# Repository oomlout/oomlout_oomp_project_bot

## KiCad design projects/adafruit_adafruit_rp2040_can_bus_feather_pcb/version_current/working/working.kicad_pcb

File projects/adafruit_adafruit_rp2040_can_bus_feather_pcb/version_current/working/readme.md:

# OOMP Project  
## Adafruit-RP2040-CAN-Bus-Feather-PCB  by adafruit  
  
oomp key: oomp_projects_flat_adafruit_adafruit_rp2040_can_bus_feather_pcb  
(snippet of original readme)  
  
-- Adafruit RP2040 CAN Bus Feather with MCP2515 CAN Controller - STEMMA QT PCB  
  
<a href="http://www.adafruit.com/products/5724"><br/>  
Click here to purchase one from the Adafruit shop</a>  
  
PCB files for the Adafruit RP2040 CAN Bus Feather with MCP2515 CAN Controller - STEMMA QT.   
  
Format is EagleCAD schematic and board layout  
* https://www.adafruit.com/product/5724  
  
--- Description  
  
If you'd like to quickly get started with CAN bus interfacing, with no soldering required, our Adafruit RP2040 CAN Bus Feather comes ready-to-rock with a microcontroller, CAN chipset and terminal blocks for instant gratification. The controller used is the MCP26525 (aka a MCP2515 with built-in transciever), an extremely popular and well-supported chipset that has drivers in Arduino and CircuitPython and only requires an SPI port and two pins for chip-select and IRQ. Use it to send and receive messages in either standard or extended format at up to 1 Mbps.  
  
Feather is the development board specification from Adafruit, and like its namesake, it is thin, light, and lets you fly! We designed Feather to be a new standard for portable microcontroller cores. We have other boards in the Feather family, check'em out here.  
  
CAN Bus is a small-scale networking standard, originally designed for cars and, yes, busses, but is now used for many robotics or sensor networks that need better range and addressing than I2C and don't have the pins or computational abil  
  full source readme at [readme_src.md](readme_src.md)  
  
source repo at: [https://github.com/adafruit/Adafruit-RP2040-CAN-Bus-Feather-PCB](https://github.com/adafruit/Adafruit-RP2040-CAN-Bus-Feather-PCB)  
## Board  

## Schematic  

[schematic pdf](working_schematic.pdf)  
## Images

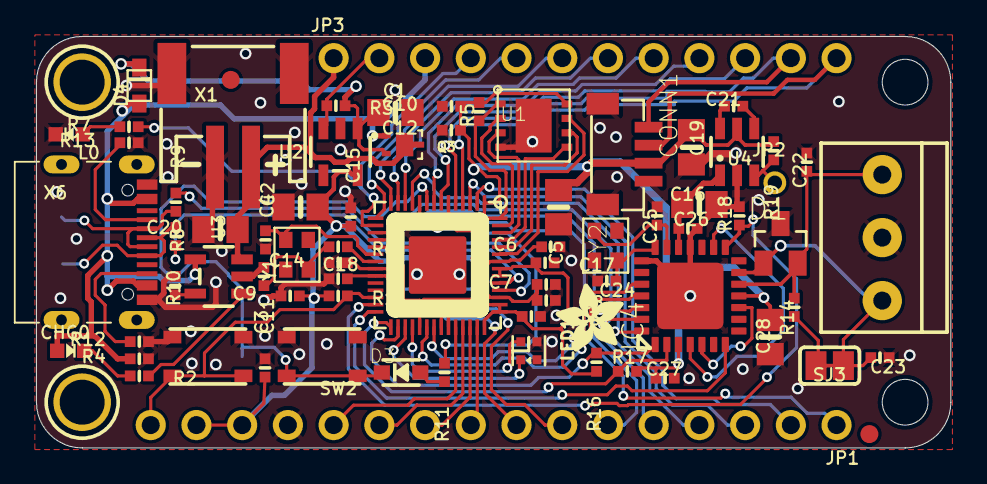
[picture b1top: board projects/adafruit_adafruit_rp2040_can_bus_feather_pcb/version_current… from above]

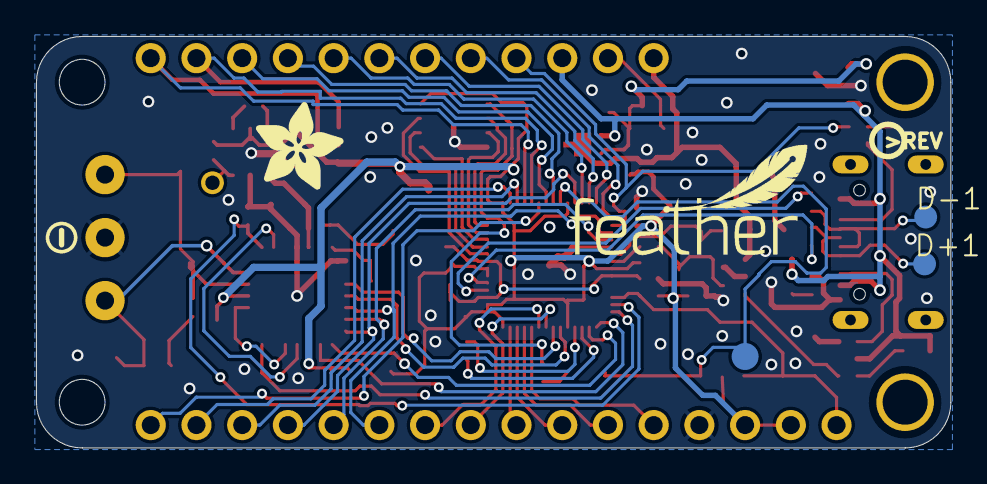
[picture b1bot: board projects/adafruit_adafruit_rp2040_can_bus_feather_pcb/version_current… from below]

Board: 2 copper layers, 50.8 x 22.9 mm, 155 parts (40 on the bottom side), 69 nets.

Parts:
@HOLE0, @HOLE1: (no value)
C1, C4, C5, C16, C19, C20, C28: 10uF/16V; 0805-NO
C2, C3, C24, C25: 22pF; _0402NO
C6, C7, C9, C12, C13, C14, C18, C26, C27: 0.1uF; _0402NO
C8, C10, C11, C15, C17, C21: 1uF/25V; _0402NO
C22, C23: 47pF; _0402NO
CHG0: ORANGE; CHIPLED_0603_NOOUTLINE
CONN1: STEMMA_I2C_QTRA; JST_SH4_RA
D1: PESD1CAN; SOT23
D3: 1N5819; SOD-323_MINI
D4: PMEG2020AEA; SOD-323F
D+1: TPB1,27; B1,27
D-1: TPB1,27; B1,27
IC1: RP2040_QFN56; QFN56_7MM_REDUCEDEPAD
IC4: MCP25625; QFN28-ML_6X6MM
JP1: 1X16_ROUND
JP2: 1X01_2MM
JP3: 1X12_ROUND
L0: RED; CHIPLED_0603_NOOUTLINE
LED1: WS2812B_SK6805_1515; SK6805_1515
NEOPIX1: 3.5mm; TERMBLOCK_1X3-3.5MM
PLABEL0: PLABEL0
PLABEL1: PLABEL1
PLABEL2: PLABEL2
PLABEL3: PLABEL3
PLABEL4: PLABEL4
PLABEL5: PLABEL5
PLABEL6: PLABEL6
PLABEL7: PLABEL7
PLABEL8: PLABEL8
PLABEL9: PLABEL9
PLABEL10: PLABEL10
PLABEL11: PLABEL11
PLABEL12: PLABEL12
PLABEL13: PLABEL13
PLABEL14: PLABEL14
PLABEL15: PLABEL15
PLABEL16: PLABEL16
PLABEL17: PLABEL17
PLABEL18: PLABEL18
PLABEL19: PLABEL19
PLABEL20: PLABEL20
PLABEL21: PLABEL21
PLABEL22: PLABEL22
PLABEL23: PLABEL23
PLABEL24: PLABEL24
PLABEL25: PLABEL25
PLABEL26: PLABEL26
PLABEL27: PLABEL27
PLABEL28: PLABEL28
PLABEL29: PLABEL29
PLABEL30: PLABEL30
PLABEL31: PLABEL31
PLABEL32: PLABEL32
PLABEL33: PLABEL33
PLABEL34: PLABEL34
PLABEL35: PLABEL35
PLABEL36: PLABEL36
PLABEL37: PLABEL37
PLABEL38: PLABEL38
PLABEL39: PLABEL39
PLABEL40: PLABEL40
PLABEL41: PLABEL41
PLABEL42: PLABEL42
PLABEL43: PLABEL43
PLABEL44: PLABEL44
PLABEL45: PLABEL45
PLABEL46: PLABEL46
PLABEL47: PLABEL47
PLABEL48: PLABEL48
PLABEL49: PLABEL49
PLABEL50: PLABEL50
PLABEL51: PLABEL51
PLABEL52: PLABEL52
PLABEL53: PLABEL53
PLABEL54: PLABEL54
PLABEL55: PLABEL55
PLABEL56: PLABEL56
PLABEL57: PLABEL57
PLABEL58: PLABEL58
PLABEL59: PLABEL59
PLABEL60: PLABEL60
PLABEL61: PLABEL61
PLABEL62: PLABEL62
PLABEL63: PLABEL63
PLABEL64: PLABEL64
PLABEL65: PLABEL65
PLABEL66: PLABEL66
PLABEL67: PLABEL67
PLABEL68: PLABEL68
PLABEL69: PLABEL69
Q3: DMG3415UFY; DFN2015-3
R1, R2, R3, R4, R5, R7, R16, R17, R18, R19: 10K; _0402NO
R6, R11: 1K; _0402NO
R8, R12, R13: 5.1K; _0402NO
R9, R10: 22 ohm; _0402NO
R14: 120; _0402NO
SJ3: SOLDERJUMPER_CLOSEDWIRE
SW1, SW2: RKB2; BTN_RKB2_4.6X2.8
TP3: TESTPOINT_ROUND_1.5MM_NO
U1: 8MB QSPI; USON8_4X4
U2: RT9080-3.3; SOT23-5
U3: MCP73831T-2ACI/OT; SOT23-5
U4: AP3602; SOT23-6
U$13: PCBFEAT-REV-040
U$31, U$32: MOUNTINGHOLE2.5; MOUNTINGHOLE_2.5_PLATED
U$34, U$35: FIDUCIAL_1MM
U$42: ADAFRUIT_3.5MM
U$53: SYMBOL_MINUS
U$54: ADAFRUIT_5MM
U$60: FEATHERLOGO_SMALL
X1: JSTPH; JSTPH2_BATT
X6: USB Type C; USB_C_CUSB31-CFM2AX-01-X
Y1: 12MHz/12pF; CRYSTAL_2.5X2
Y2: 16MHz 12pF; CRYSTAL_2.5X2

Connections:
1.2V: C6.2, C7.2, C8.1, C18.2, IC1.23, IC1.45, IC1.50
5.0V: C16.1, C26.2, IC4.19, U4.1
5V_SHDN: JP2.1, R19.2, U4.3
+3V3: C4.1, C5.1, C9.1, C10.1, C11.1, C12.1, C13.1, C14.1, C15.1, C17.1, C19.1, C27.2, C28.1, CONN1.2, IC1.1, IC1.10, IC1.22, IC1.33, IC1.42, IC1.43, IC1.44, IC1.48, IC1.49, IC4.3, IC4.11, JP1.14, JP1.15, R1.1, R5.2, R16.2, R17.2, R19.1, U1.8, U2.5, U4.5
A0: IC1.38, JP1.12
A1: IC1.39, JP1.11
A2: IC1.40, JP1.10
A3: IC1.41, JP1.9
CAN_CS: IC1.30, IC4.1, R16.1
CAN_H: C23.1, D1.1, IC4.13, NEOPIX1.3, SJ3.2
CAN_INT: IC1.34, IC4.25
CAN_L: C22.2, D1.2, IC4.12, NEOPIX1.1, R14.1
CAN_RESET: IC1.29, IC4.2, R17.1
CAN_STBY: IC1.27, IC4.15, R18.1
CC1: R13.2, X6.A5
CC2: R12.2, X6.B5
D4: IC1.6, JP1.1
D5: IC1.7, JP3.10
D6: IC1.8, JP3.9
D9: IC1.12, JP3.8
D10: IC1.13, JP3.7
D11: IC1.14, JP3.6
D12: IC1.15, JP3.5
D13: IC1.16, JP3.4, R7.1
D24: IC1.36, JP1.8
D25: IC1.37, JP1.7
D+: IC1.47, R10.2
D-: IC1.46, R9.2
EN: JP3.2, R3.1, U2.3
GND: C1.2, C2.1, C3.1, C4.2, C5.2, C6.1, C7.1, C8.2, C9.2, C10.2, C11.2, C12.2, C13.2, C14.2, C15.2, C16.2, C17.2, C18.1, C19.2, C20.2, C22.1, C23.2, C24.1, C25.1, C26.1, C27.1, C28.2, CONN1.1, CONN1.MT1, CONN1.MT2, D1.3, IC1.19, IC1.P$1, IC4.18, IC4.22, IC4.EXP, JP1.13, L0.C, LED1.4, NEOPIX1.2, R4.1, R8.2, R12.1, R13.1, R18.2, SW1.B, SW1.B', SW2.B, SW2.B', U1.4, U1.PAD, U2.2, U3.2, U4.2, X1.1, X1.NC1, X1.NC2, X6.A1B12, X6.B1A12
MISO: IC1.11, IC4.28, JP1.4
MOSI: IC1.18, IC4.27, JP1.5
unnamed: CHG0.C, R2.1
unnamed: L0.A, R7.2
unnamed: R2.2, U3.1
unnamed: R8.1, U3.5
unnamed: C2.2, IC1.20, Y1.3
unnamed: C3.2, R6.1, Y1.1
unnamed: IC1.21, R6.2
unnamed: C21.1, U4.4
unnamed: C21.2, U4.6
unnamed: R14.2, SJ3.1
unnamed: IC4.5, IC4.10
unnamed: IC4.4, IC4.16
unnamed: D3.A, R11.2
NEOPIXEL: IC1.32, LED1.1
NEOPIX_PWR: IC1.31, LED1.2
OSC1: C24.2, IC4.21, Y2.3
OSC2: C25.2, IC4.20, Y2.1
QSPI_CS: IC1.56, R5.1, R11.1, U1.1
QSPI_DATA[0]: IC1.53, U1.5
QSPI_DATA[1]: IC1.55, U1.2
QSPI_DATA[2]: IC1.54, U1.3
QSPI_DATA[3]: IC1.51, U1.7
QSPI_SCK: IC1.52, U1.6
RX: IC1.3, JP1.3
RX0BF: IC1.35, IC4.24
SCK: IC1.17, IC4.26, JP1.6
SCL: CONN1.4, IC1.5, JP3.11
SDA: CONN1.3, IC1.4, JP3.12
TX: IC1.2, JP1.2
TX0RTS: IC1.28, IC4.7
USBBOOT: D3.C, IC1.9, SW2.A, SW2.A', TP3.P$1
USB_D+: D+1.TP, R10.1, X6.A6, X6.B6
USB_D-: D-1.TP, R9.1, X6.A7, X6.B7
VBAT: C20.1, JP3.1, Q3.3, U3.3, X1.2
VBUS: CHG0.A, D4.A, JP3.3, Q3.1, R4.2, U3.4, X6.A4B9, X6.B4A9
VHI: C1.1, D4.C, Q3.2, R3.2, U2.1
~RESET: IC1.26, JP1.16, R1.2, SW1.A, SW1.A'

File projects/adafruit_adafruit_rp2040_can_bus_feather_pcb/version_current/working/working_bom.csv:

"Id";"Designator";"Footprint";"Quantity";"Designation";"Supplier and ref";
1;"C14,C13,C26,C27,C18,C6,C7,C9,C12";"_0402NO";9;"0.1uF";;;
2;"C15,C8,C17,C10,C21,C11";"_0402NO";6;"1uF/25V";;;
3;"PLABEL5";"PLABEL5";1;"";;;
4;"L0";"CHIPLED_0603_NOOUTLINE";1;"RED";;;
5;"@HOLE0,@HOLE1";"";2;"";;;
6;"PLABEL3";"PLABEL3";1;"";;;
7;"C1,C20,C5,C28,C16,C4,C19";"0805-NO";7;"10uF/16V";;;
8;"R18,R2,R17,R4,R5,R3,R1,R7,R16,R19";"_0402NO";10;"10K";;;
9;"PLABEL33";"PLABEL33";1;"";;;
10;"CHG0";"CHIPLED_0603_NOOUTLINE";1;"ORANGE";;;
11;"PLABEL26";"PLABEL26";1;"";;;
12;"PLABEL21";"PLABEL21";1;"";;;
13;"SW1,SW2";"BTN_RKB2_4.6X2.8";2;"RKB2";;;
14;"Q3";"DFN2015-3";1;"DMG3415UFY";;;
15;"PLABEL19";"PLABEL19";1;"";;;
16;"U$42";"ADAFRUIT_3.5MM";1;"";;;
17;"PLABEL23";"PLABEL23";1;"";;;
18;"U1";"USON8_4X4";1;"8MB QSPI";;;
19;"PLABEL4";"PLABEL4";1;"";;;
20;"PLABEL8";"PLABEL8";1;"";;;
21;"PLABEL0";"PLABEL0";1;"";;;
22;"SJ3";"SOLDERJUMPER_CLOSEDWIRE";1;"";;;
23;"JP3";"1X12_ROUND";1;"";;;
24;"PLABEL34";"PLABEL34";1;"";;;
25;"IC1";"QFN56_7MM_REDUCEDEPAD";1;"RP2040_QFN56";;;
26;"D4";"SOD-323F";1;"PMEG2020AEA";;;
27;"PLABEL15";"PLABEL15";1;"";;;
28;"JP1";"1X16_ROUND";1;"";;;
29;"R11,R6";"_0402NO";2;"1K";;;
30;"D1";"SOT23";1;"PESD1CAN";;;
31;"PLABEL24";"PLABEL24";1;"";;;
32;"U4";"SOT23-6";1;"AP3602";;;
33;"PLABEL27";"PLABEL27";1;"";;;
34;"R13,R12,R8";"_0402NO";3;"5.1K";;;
35;"C3,C25,C24,C2";"_0402NO";4;"22pF";;;
36;"PLABEL1";"PLABEL1";1;"";;;
37;"Y2";"CRYSTAL_2.5X2";1;"16MHz 12pF";;;
38;"Y1";"CRYSTAL_2.5X2";1;"12MHz/12pF";;;
39;"PLABEL25";"PLABEL25";1;"";;;
40;"PLABEL2";"PLABEL2";1;"";;;
41;"CONN1";"JST_SH4_RA";1;"STEMMA_I2C_QTRA";;;
42;"PLABEL30";"PLABEL30";1;"";;;
43;"X6";"USB_C_CUSB31-CFM2AX-01-X";1;"USB Type C";;;
44;"PLABEL12";"PLABEL12";1;"";;;
45;"U$32,U$31";"MOUNTINGHOLE_2.5_PLATED";2;"MOUNTINGHOLE2.5";;;
46;"PLABEL35";"PLABEL35";1;"";;;
47;"PLABEL6";"PLABEL6";1;"";;;
48;"PLABEL31";"PLABEL31";1;"";;;
49;"R14";"_0402NO";1;"120";;;
50;"PLABEL14";"PLABEL14";1;"";;;
51;"R9,R10";"_0402NO";2;"22 ohm";;;
52;"X1";"JSTPH2_BATT";1;"JSTPH";;;
53;"PLABEL17";"PLABEL17";1;"";;;
54;"U3";"SOT23-5";1;"MCP73831T-2ACI/OT";;;
55;"D3";"SOD-323_MINI";1;"1N5819";;;
56;"PLABEL9";"PLABEL9";1;"";;;
57;"PLABEL11";"PLABEL11";1;"";;;
58;"PLABEL16";"PLABEL16";1;"";;;
59;"LED1";"SK6805_1515";1;"WS2812B_SK6805_1515";;;
60;"U2";"SOT23-5";1;"RT9080-3.3";;;
61;"PLABEL7";"PLABEL7";1;"";;;
62;"U$34,U$35";"FIDUCIAL_1MM";2;"FIDUCIAL_1MM";;;
63;"PLABEL10";"PLABEL10";1;"";;;
64;"PLABEL28";"PLABEL28";1;"";;;
65;"PLABEL32";"PLABEL32";1;"";;;
66;"JP2";"1X01_2MM";1;"";;;
67;"C23,C22";"_0402NO";2;"47pF";;;
68;"PLABEL18";"PLABEL18";1;"";;;
69;"PLABEL29";"PLABEL29";1;"";;;
70;"PLABEL20";"PLABEL20";1;"";;;
71;"PLABEL22";"PLABEL22";1;"";;;
72;"PLABEL36";"PLABEL36";1;"";;;
73;"NEOPIX1";"TERMBLOCK_1X3-3.5MM";1;"3.5mm";;;
74;"PLABEL13";"PLABEL13";1;"";;;
75;"IC4";"QFN28-ML_6X6MM";1;"MCP25625";;;
76;"PLABEL42";"PLABEL42";1;"";;;
77;"PLABEL44";"PLABEL44";1;"";;;
78;"PLABEL64";"PLABEL64";1;"";;;
79;"U$13";"PCBFEAT-REV-040";1;"";;;
80;"PLABEL40";"PLABEL40";1;"";;;
81;"U$53";"SYMBOL_MINUS";1;"";;;
82;"PLABEL62";"PLABEL62";1;"";;;
83;"PLABEL47";"PLABEL47";1;"";;;
84;"PLABEL48";"PLABEL48";1;"";;;
85;"PLABEL58";"PLABEL58";1;"";;;
86;"PLABEL59";"PLABEL59";1;"";;;
87;"TP3";"TESTPOINT_ROUND_1.5MM_NO";1;"";;;
88;"PLABEL56";"PLABEL56";1;"";;;
89;"PLABEL63";"PLABEL63";1;"";;;
90;"PLABEL53";"PLABEL53";1;"";;;
91;"PLABEL69";"PLABEL69";1;"";;;
92;"PLABEL51";"PLABEL51";1;"";;;
93;"PLABEL50";"PLABEL50";1;"";;;
94;"PLABEL37";"PLABEL37";1;"";;;
95;"PLABEL67";"PLABEL67";1;"";;;
96;"U$60";"FEATHERLOGO_SMALL";1;"";;;
97;"PLABEL65";"PLABEL65";1;"";;;
98;"PLABEL54";"PLABEL54";1;"";;;
99;"PLABEL38";"PLABEL38";1;"";;;
100;"PLABEL55";"PLABEL55";1;"";;;
101;"PLABEL57";"PLABEL57";1;"";;;
102;"PLABEL66";"PLABEL66";1;"";;;
103;"PLABEL49";"PLABEL49";1;"";;;
104;"PLABEL68";"PLABEL68";1;"";;;
105;"D+1,D-1";"B1,27";2;"TPB1,27";;;
106;"U$54";"ADAFRUIT_5MM";1;"";;;
107;"PLABEL61";"PLABEL61";1;"";;;
108;"PLABEL43";"PLABEL43";1;"";;;
109;"PLABEL52";"PLABEL52";1;"";;;
110;"PLABEL60";"PLABEL60";1;"";;;
111;"PLABEL46";"PLABEL46";1;"";;;
112;"PLABEL45";"PLABEL45";1;"";;;
113;"PLABEL39";"PLABEL39";1;"";;;
114;"PLABEL41";"PLABEL41";1;"";;;

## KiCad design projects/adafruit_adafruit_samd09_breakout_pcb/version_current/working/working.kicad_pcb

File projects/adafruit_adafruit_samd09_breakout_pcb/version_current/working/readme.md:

# OOMP Project  
## Adafruit-SAMD09-Breakout-PCB  by adafruit  
  
oomp key: oomp_projects_flat_adafruit_adafruit_samd09_breakout_pcb  
(snippet of original readme)  
  
-- Adafruit SAMD09 Breakout PCB  
  
<a href="http://www.adafruit.com/products/3657"><br/>  
Click here to purchase one from the Adafruit shop</a>  
  
PCB files for the Adafruit SAMD09 microcontroller breakout  
  
Format is EagleCAD schematic and board layout  
  
For more details, check out the product page at  
* https://www.adafruit.com/products/3657  
  
--- Description  
  
Adafruit seesaw is a near-universal converter framework which allows you to add add and extend hardware support to any I2C-capable microcontroller or microcomputer. Instead of getting separate I2C GPIO expanders, ADCs, PWM drivers, etc, seesaw can be configured to give a wide range of capabilities.  
  
For example, our ATSAMD09 breakout with seesaw gives you  
  
* 3 x 12-bit ADC inputs  
* 3 x 8-bit PWM outputs  
* 7 x GPIO with selectable pullup or pulldown  
* 1 x NeoPixel output (up to 340 pixels)  
* 1 x EEPROM with 64 byte of NVM memory (handy for storing small access tokens or MAC addresses)  
* 1 x Interrupt output that can be triggered by any of the accessories  
* 2 x I2C address selection pins  
* 1 x Activity LED  
  
But you can reprogram and reconfigure the chip to have more or less of each peripheral - as long as it fits into the ATSAMD09D14's firmware! For example, there's also a UART converter but it isn't included in the default firmware.  
  
The ATSAMD09 breakout is great for development of seesaw capabilities (we use it in-house for our design work) or you can use it as-is to give you  
  full source readme at [readme_src.md](readme_src.md)  
  
source repo at: [https://github.com/adafruit/Adafruit-SAMD09-Breakout-PCB](https://github.com/adafruit/Adafruit-SAMD09-Breakout-PCB)  
## Board  

## Schematic  

[schematic pdf](working_schematic.pdf)  
## Images

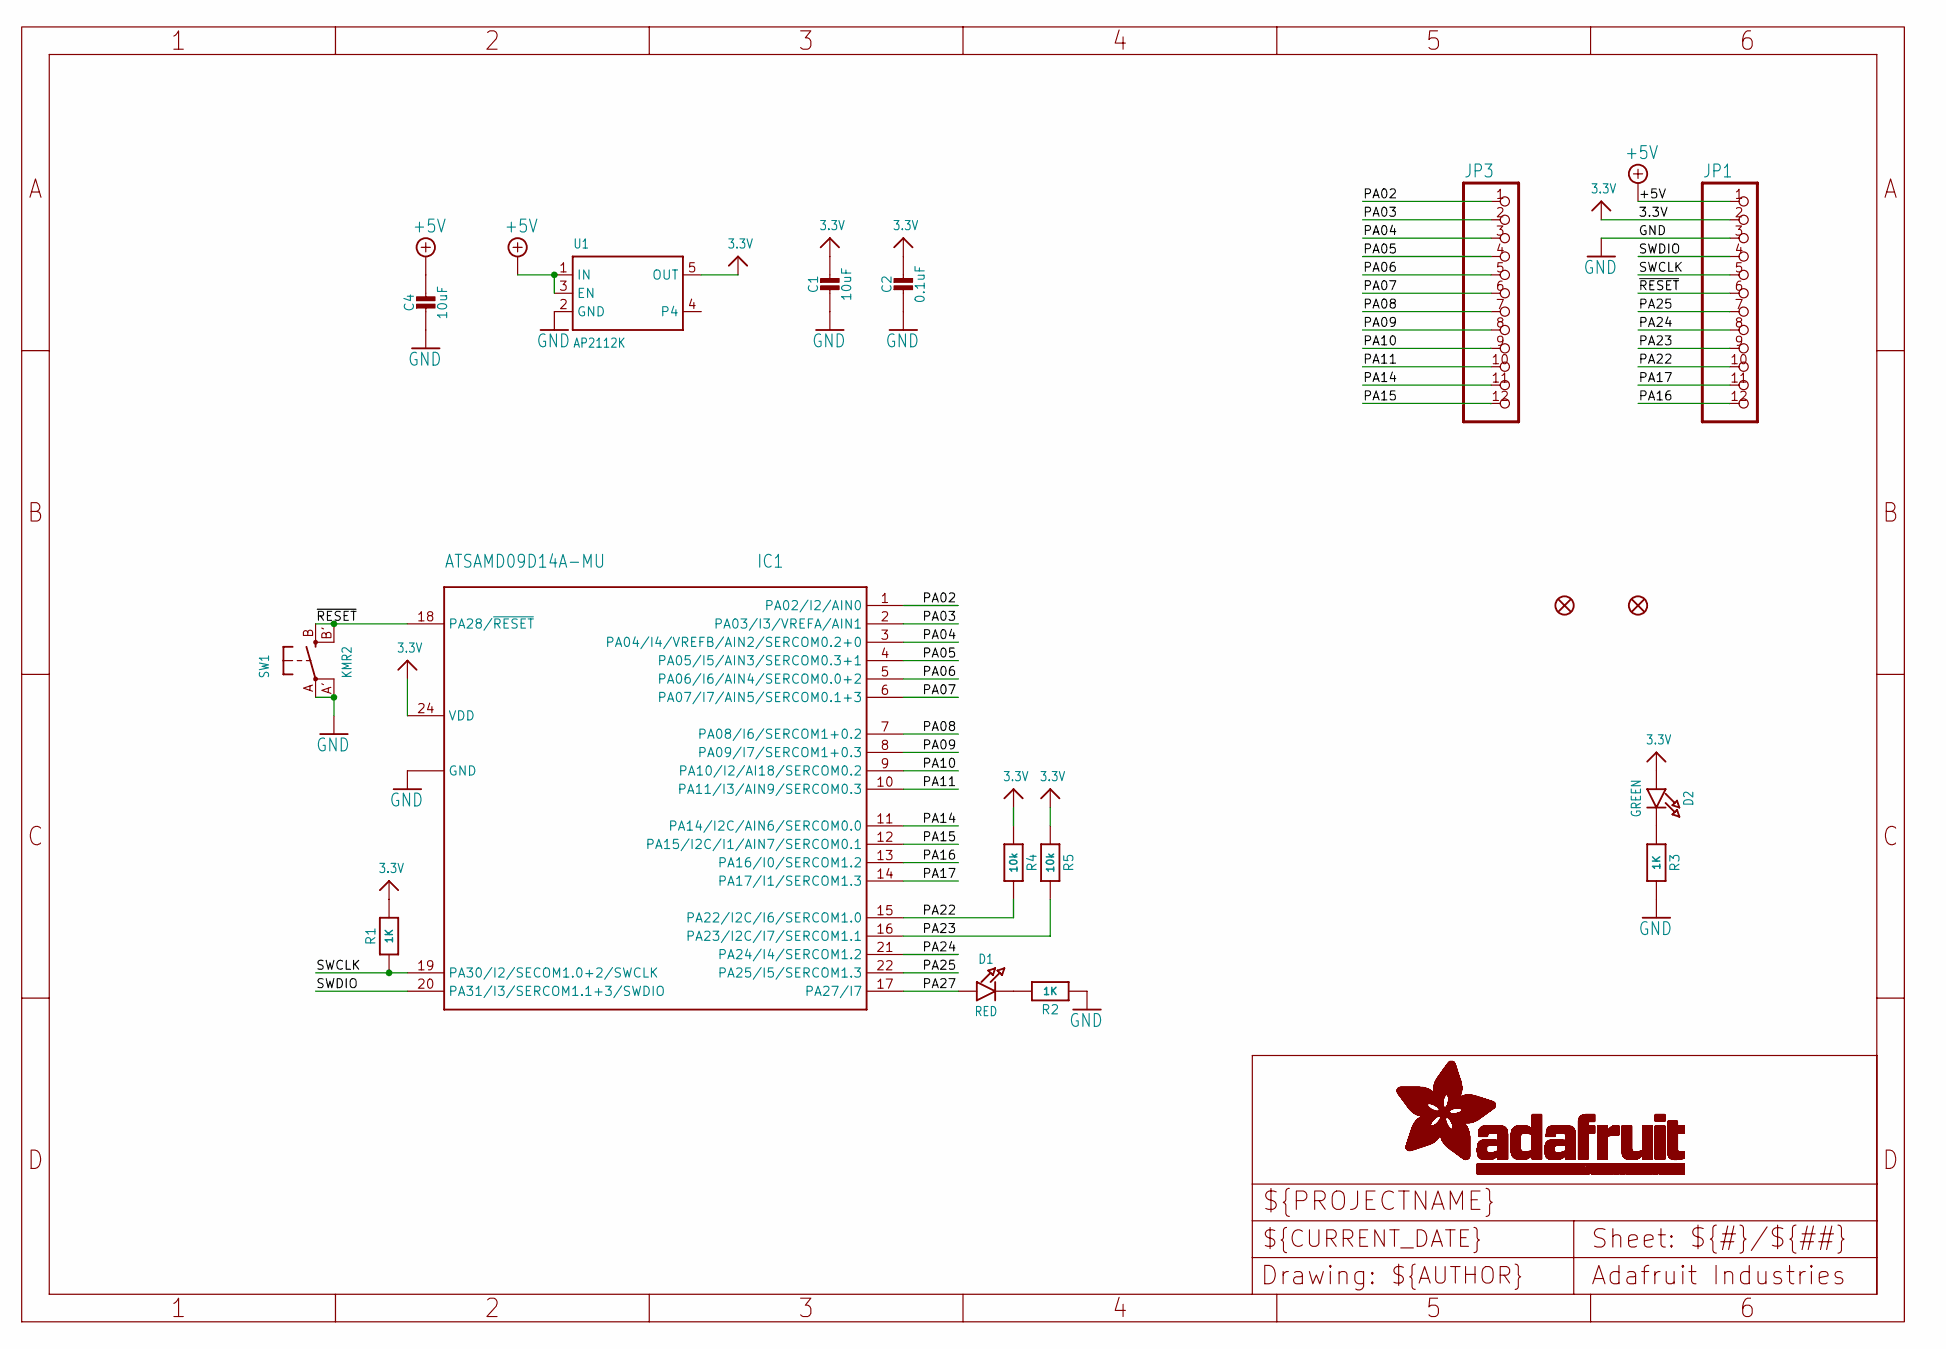
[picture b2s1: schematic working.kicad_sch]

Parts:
C1, C4: 10uF; 0805-NO
C2: 0.1uF; 0603-NO
D1: RED; CHIPLED_0805_NOOUTLINE
D2: GREEN; CHIPLED_0805_NOOUTLINE
FID1, FID2: FIDUCIAL""; FIDUCIAL_1MM
IC1: ATSAMD09D14A-MU; QFN24_4MM
JP1, JP3: HEADER-1X1276MIL; 1X12_ROUND_76MIL
R1, R2, R3: 1K; 0603-NO
R4, R5: 10k; 0603-NO
SW1: KMR2; BTN_KMR2_4.6X2.8
U1: AP2112K; SOT23-5

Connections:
3.3V: C1.1, C2.1, D2.A, IC1.24 (VDD), JP1.2, R1.2, R4.1, R5.1, U1.5 (OUT)
+5V: C4.1, JP1.1, U1.1 (IN), U1.3 (EN)
GND: C1.2, C2.2, C4.2, IC1.23 (GND), IC1.THERM (GND), JP1.3, R2.1, R3.2, SW1.A, SW1.A' (P1), U1.2 (GND)
unnamed: D1.C, R2.2
unnamed: D2.C, R3.1
PA02: IC1.1 (PA02/I2/AIN0), JP3.1
PA03: IC1.2 (PA03/I3/VREFA/AIN1), JP3.2
PA04: IC1.3 (PA04/I4/VREFB/AIN2/SERCOM0.2+0), JP3.3
PA05: IC1.4 (PA05/I5/AIN3/SERCOM0.3+1), JP3.4
PA06: IC1.5 (PA06/I6/AIN4/SERCOM0.0+2), JP3.5
PA07: IC1.6 (PA07/I7/AIN5/SERCOM0.1+3), JP3.6
PA08: IC1.7 (PA08/I6/SERCOM1+0.2), JP3.7
PA09: IC1.8 (PA09/I7/SERCOM1+0.3), JP3.8
PA10: IC1.9 (PA10/I2/AI18/SERCOM0.2), JP3.9
PA11: IC1.10 (PA11/I3/AIN9/SERCOM0.3), JP3.10
PA14: IC1.11 (PA14/I2C/AIN6/SERCOM0.0), JP3.11
PA15: IC1.12 (PA15/I2C/I1/AIN7/SERCOM0.1), JP3.12
PA16: IC1.13 (PA16/I0/SERCOM1.2), JP1.12
PA17: IC1.14 (PA17/I1/SERCOM1.3), JP1.11
PA22: IC1.15 (PA22/I2C/I6/SERCOM1.0), JP1.10, R4.2
PA23: IC1.16 (PA23/I2C/I7/SERCOM1.1), JP1.9, R5.2
PA24: IC1.21 (PA24/I4/SERCOM1.2), JP1.8
PA25: IC1.22 (PA25/I5/SERCOM1.3), JP1.7
PA27: D1.A, IC1.17 (PA27/I7)
SWCLK: IC1.19 (PA30/I2/SECOM1.0+2/SWCLK), JP1.5, R1.1
SWDIO: IC1.20 (PA31/I3/SERCOM1.1+3/SWDIO), JP1.4
~RESET: IC1.18 (PA28/~RESET), JP1.6, SW1.B (S), SW1.B' (S1)

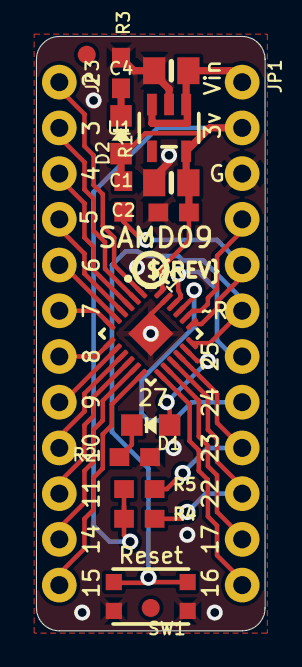
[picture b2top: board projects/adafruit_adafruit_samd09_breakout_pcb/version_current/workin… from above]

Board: 2 copper layers, 12.7 x 33.0 mm, 19 parts (1 on the bottom side), 27 nets.

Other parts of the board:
U$7: SEESAW_LOGO
U$12: PCBFEAT-REV-040

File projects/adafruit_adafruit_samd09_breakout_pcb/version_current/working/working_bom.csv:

Row,Description,Part,References,Value,Footprint,Quantity Per PCB,Status,Datasheet
1,,CAP_CERAMIC0603_NO,C2,0.1uF,0603-NO,1, ,
2,,CAP_CERAMIC0805-NOOUTLINE,C1 C4,10uF,0805-NO,2, ,
3,,LED0805_NOOUTLINE,D2,GREEN,CHIPLED_0805_NOOUTLINE,1, ,
4,,LED0805_NOOUTLINE,D1,RED,CHIPLED_0805_NOOUTLINE,1, ,
5,,ATSAMD09D14A-MU,IC1,ATSAMD09D14A-MU,QFN24_4MM,1, ,
6,,HEADER-1X1276MIL,JP1 JP3,HEADER-1X1276MIL,1X12_ROUND_76MIL,2, ,
7,,RESISTOR_0603_NOOUT,R1 R2 R3,1K,0603-NO,3, ,
8,,RESISTOR_0603_NOOUT,R4 R5,10k,0603-NO,2, ,
9,,SWITCH_TACT_SMT4.6X2.8,SW1,KMR2,BTN_KMR2_4.6X2.8,1, ,
10,,VREG_SOT23-5,U1,AP2112K,SOT23-5,1, ,





Project info:
Schematic:,working
Variant:,default
Revision:,
Date:,2023-08-03_17-21-23
KiCad Version:,7.0.6-7.0.6~ubuntu22.04.1
Statistics:
Component Groups:,10
Component Count:,15 (0 SMD/ 0 THT)
Fitted Components:,15 (0 SMD/ 0 THT)
Number of PCBs:,1
Total Components:,15

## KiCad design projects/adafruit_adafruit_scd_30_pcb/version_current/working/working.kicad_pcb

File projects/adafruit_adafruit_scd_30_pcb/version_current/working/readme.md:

# OOMP Project  
## Adafruit-SCD-30-PCB  by adafruit  
  
oomp key: oomp_projects_flat_adafruit_adafruit_scd_30_pcb  
(snippet of original readme)  
  
-- Adafruit SCD-30 NDIR CO2 Temperature and Humidity Sensor PCB  
  
<a href="http://www.adafruit.com/products/4867"><br/>  
Click here to purchase one from the Adafruit shop</a>  
  
PCB files for the Adafruit SCD-30 NDIR CO2 Temperature and Humidity Sensor.   
  
Format is EagleCAD schematic and board layout  
* https://www.adafruit.com/product/4867  
  
--- Description  
  
INSERT PRODUCT COPY HERE  
  
--- License  
  
Adafruit invests time and resources providing this open source design, please support Adafruit and open-source hardware by purchasing products from [Adafruit](https://www.adafruit.com)!  
  
Designed by Limor Fried/Ladyada for Adafruit Industries.  
  
Creative Commons Attribution/Share-Alike, all text above must be included in any redistribution.   
See license.txt for additional details.  
  
  full source readme at [readme_src.md](readme_src.md)  
  
source repo at: [https://github.com/adafruit/Adafruit-SCD-30-PCB](https://github.com/adafruit/Adafruit-SCD-30-PCB)  
## Board  

## Schematic  

[schematic pdf](working_schematic.pdf)  
## Images

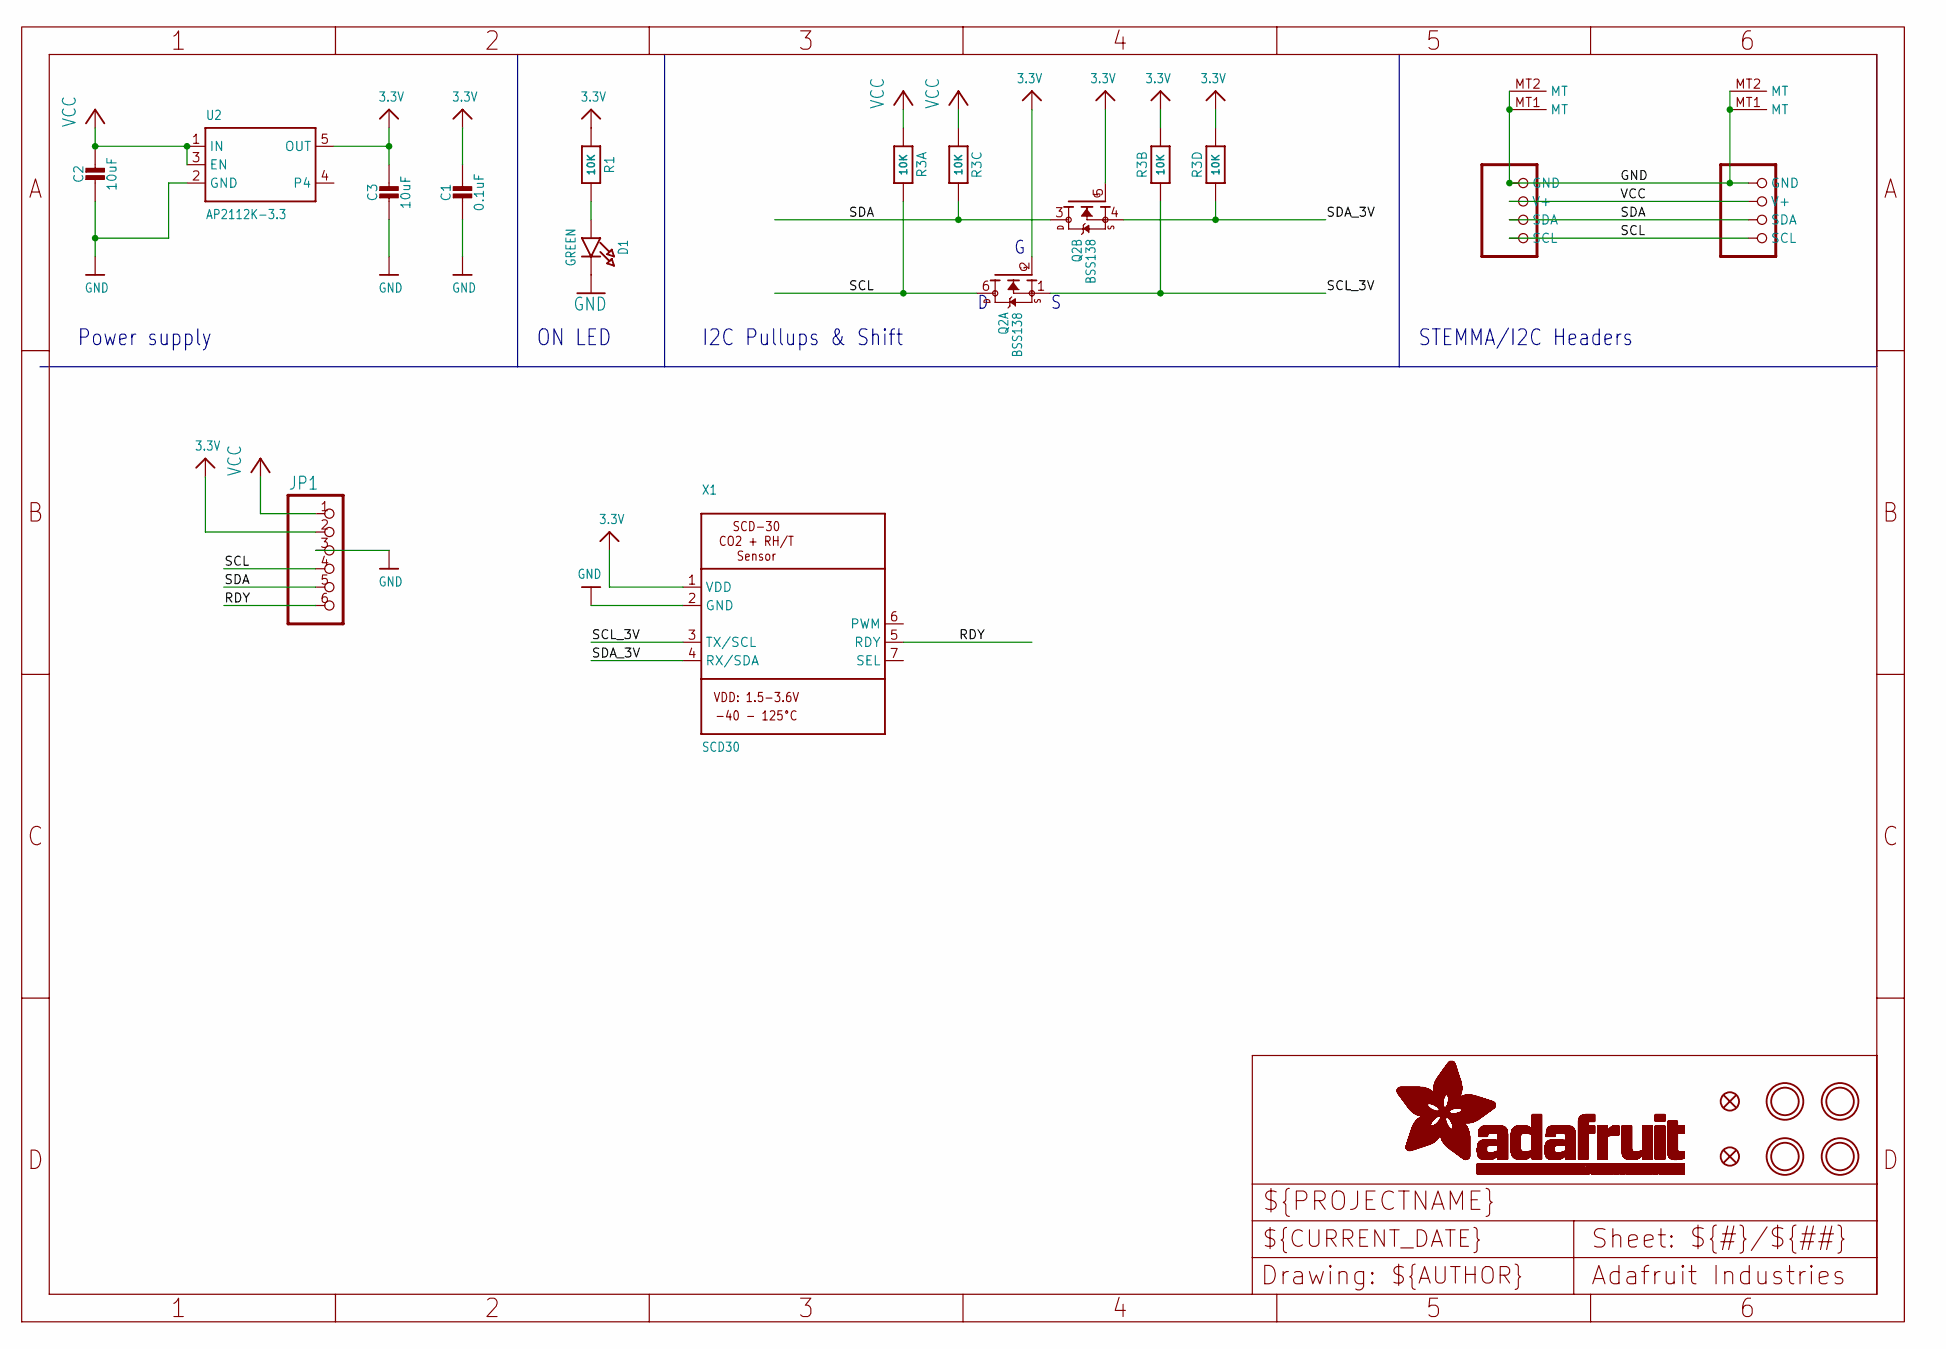
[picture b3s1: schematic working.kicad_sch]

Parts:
C1: 0.1uF; 0603-NO
C2, C3: 10uF; 0805-NO
CONN3, CONN4: STEMMA_I2C_QT; JST_SH4
D1: GREEN; CHIPLED_0603_NOOUTLINE
FID3, FID4: FIDUCIAL_1MM
JP1: HEADER-1X670MIL; 1X06_ROUND_70
Q2: BSS138; SOT363
R1: 10K; 0603-NO
R3: 10K; RESPACK_4X0603
U2: AP2112K-3.3; SOT23-5
U$1, U$17, U$19, U$21: MOUNTINGHOLE2.5; MOUNTINGHOLE_2.5_PLATED
X1: SCD30

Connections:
3.3V: C1.1, C3.1, JP1.2, Q2.2 (G), Q2.5 (G), R1.1, R3.2 (1), R3.4 (1), U2.5 (OUT), X1.1 (VDD)
GND: C1.2, C2.2, C3.2, CONN3.1 (GND), CONN3.MT1 (MT), CONN3.MT2 (MT), CONN4.1 (GND), CONN4.MT1 (MT), CONN4.MT2 (MT), D1.C, JP1.3, U2.2 (GND), X1.2 (GND)
unnamed: D1.A, R1.2
RDY: JP1.6, X1.5 (RDY)
SCL: CONN3.4 (SCL), CONN4.4 (SCL), JP1.4, Q2.6 (D), R3.8 (2)
SCL_3V: Q2.1 (S), R3.7 (2), X1.3 (TX/SCL)
SDA: CONN3.3 (SDA), CONN4.3 (SDA), JP1.5, Q2.3 (D), R3.6 (2)
SDA_3V: Q2.4 (S), R3.5 (2), X1.4 (RX/SDA)
VCC: C2.1, CONN3.2 (V+), CONN4.2 (V+), JP1.1, R3.1, R3.3 (1), U2.1 (IN), U2.3 (EN)

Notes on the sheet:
ON LED
STEMMA/I2C Headers
Power supply
I2C Pullups & Shift

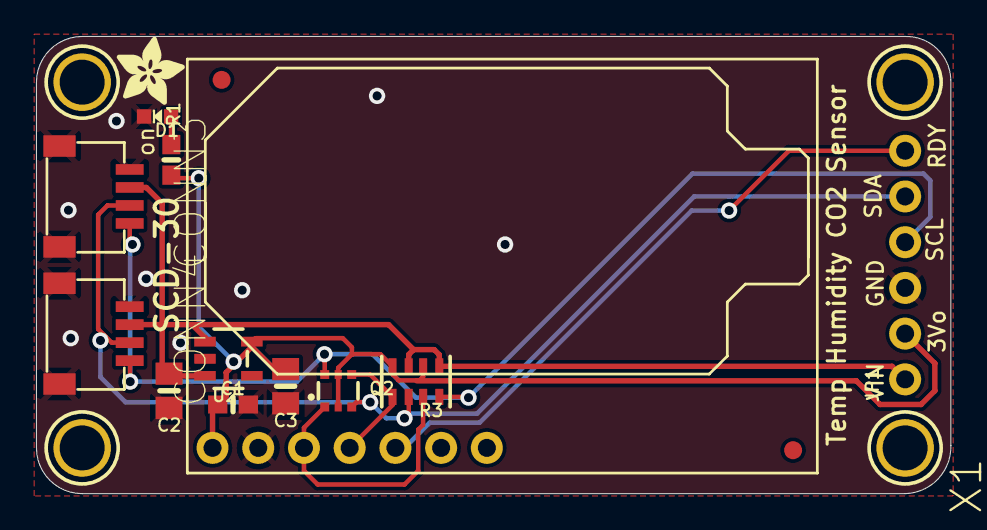
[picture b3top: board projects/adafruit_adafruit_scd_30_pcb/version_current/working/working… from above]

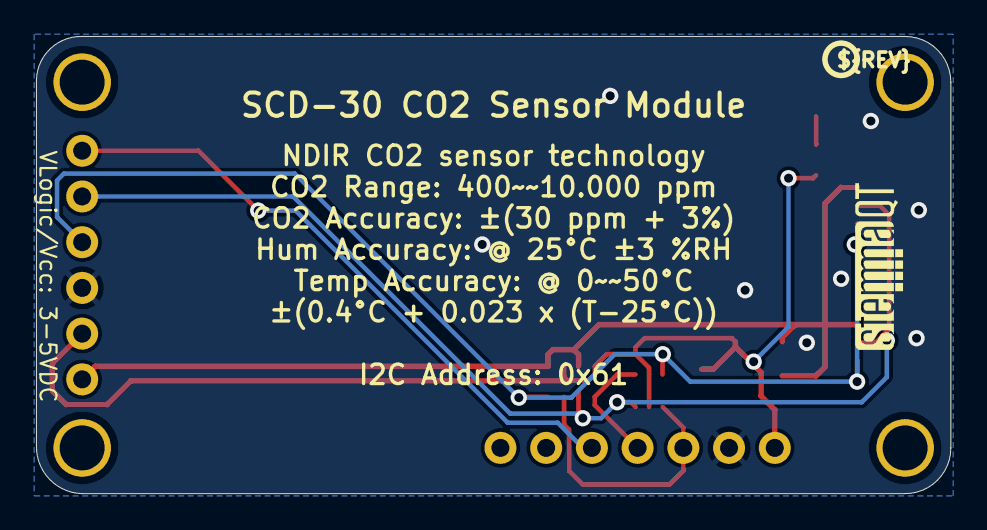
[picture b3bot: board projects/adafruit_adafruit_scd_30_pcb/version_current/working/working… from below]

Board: 2 copper layers, 50.8 x 25.4 mm, 21 parts (2 on the bottom side), 9 nets.

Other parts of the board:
U$22: ADAFRUIT_3.5MM
U$25: PCBFEAT-REV-040
U$30: STEMMAQT

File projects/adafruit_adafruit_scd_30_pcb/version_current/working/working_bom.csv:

Row,Description,Part,References,Value,Footprint,Quantity Per PCB,Status,Datasheet
1,,CAP_CERAMIC0603_NO,C1,0.1uF,0603-NO,1, ,
2,,CAP_CERAMIC0805-NOOUTLINE,C2 C3,10uF,0805-NO,2, ,
3,,STEMMA_I2C_QT,CONN3 CONN4,STEMMA_I2C_QT,JST_SH4,2, ,
4,,LED0603_NOOUTLINE,D1,GREEN,CHIPLED_0603_NOOUTLINE,1, ,
5,,HEADER-1X670MIL,JP1,HEADER-1X670MIL,1X06_ROUND_70,1, ,
6,,MOSFET-N_DUAL,Q2,BSS138,SOT363,1, ,
7,,RESISTOR_0603_NOOUT,R1,10K,0603-NO,1, ,
8,,RESISTOR_4PACK,R3,10K,RESPACK_4X0603,1, ,
9,,VREG_SOT23-5,U2,AP2112K-3.3,SOT23-5,1, ,
10,,SCD30,X1,SCD30,SCD30,1, ,





Project info:
Schematic:,working
Variant:,default
Revision:,
Date:,2023-08-03_17-21-23
KiCad Version:,7.0.6-7.0.6~ubuntu22.04.1
Statistics:
Component Groups:,10
Component Count:,12 (0 SMD/ 0 THT)
Fitted Components:,12 (0 SMD/ 0 THT)
Number of PCBs:,1
Total Components:,12

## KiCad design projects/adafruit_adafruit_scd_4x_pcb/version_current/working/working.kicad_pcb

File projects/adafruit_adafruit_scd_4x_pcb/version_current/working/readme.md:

# OOMP Project  
## Adafruit-SCD-4x-PCB  by adafruit  
  
oomp key: oomp_projects_flat_adafruit_adafruit_scd_4x_pcb  
(snippet of original readme)  
  
-- Adafruit SCD-4x CO2, Temperature and Humidity Sensor PCB  
  
<br/>  
<br/>  
Click above to purchase one from the Adafruit shop!  
  
PCB files for the Adafruit SCD-4x CO2, Temperature and Humidity Sensor.   
  
Format is EagleCAD schematic and board layout  
* https://www.adafruit.com/product/5190  
  
--- Description  
  
Take a deep breath in...now slowly breathe out. Mmm isn't it wonderful? All that air around us, which we bring into our lungs, extracts oxygen from and then breathes out carbon dioxide. CO2 is essential for life on this planet we call Earth - we and plants take turns using and emitting CO2 in an elegant symbiosis. But it's important to keep that CO2 balanced - you don't want too much around, not good for humans and not good for our planet.  
  
The SCD-40 is a photoacoustic 'true' CO2 sensor that will tell you the CO2 PPM (parts-per-million) composition of ambient air. Unlike the SGP30, this sensor isn't approximating it from VOC gas concentration - it really is measuring the CO2 concentration! That means it's bigger and more expensive, but it is the real thing. Perfect for environmental sensing, scientific experiments, air quality and ventilation studies, and more.  
  
Compared to the illustrious SCD-30, this sensor uses a different measurement technique, which allows it to be much s  
  full source readme at [readme_src.md](readme_src.md)  
  
source repo at: [https://github.com/adafruit/Adafruit-SCD-4x-PCB](https://github.com/adafruit/Adafruit-SCD-4x-PCB)  
## Board  

## Schematic  

[schematic pdf](working_schematic.pdf)  
## Images

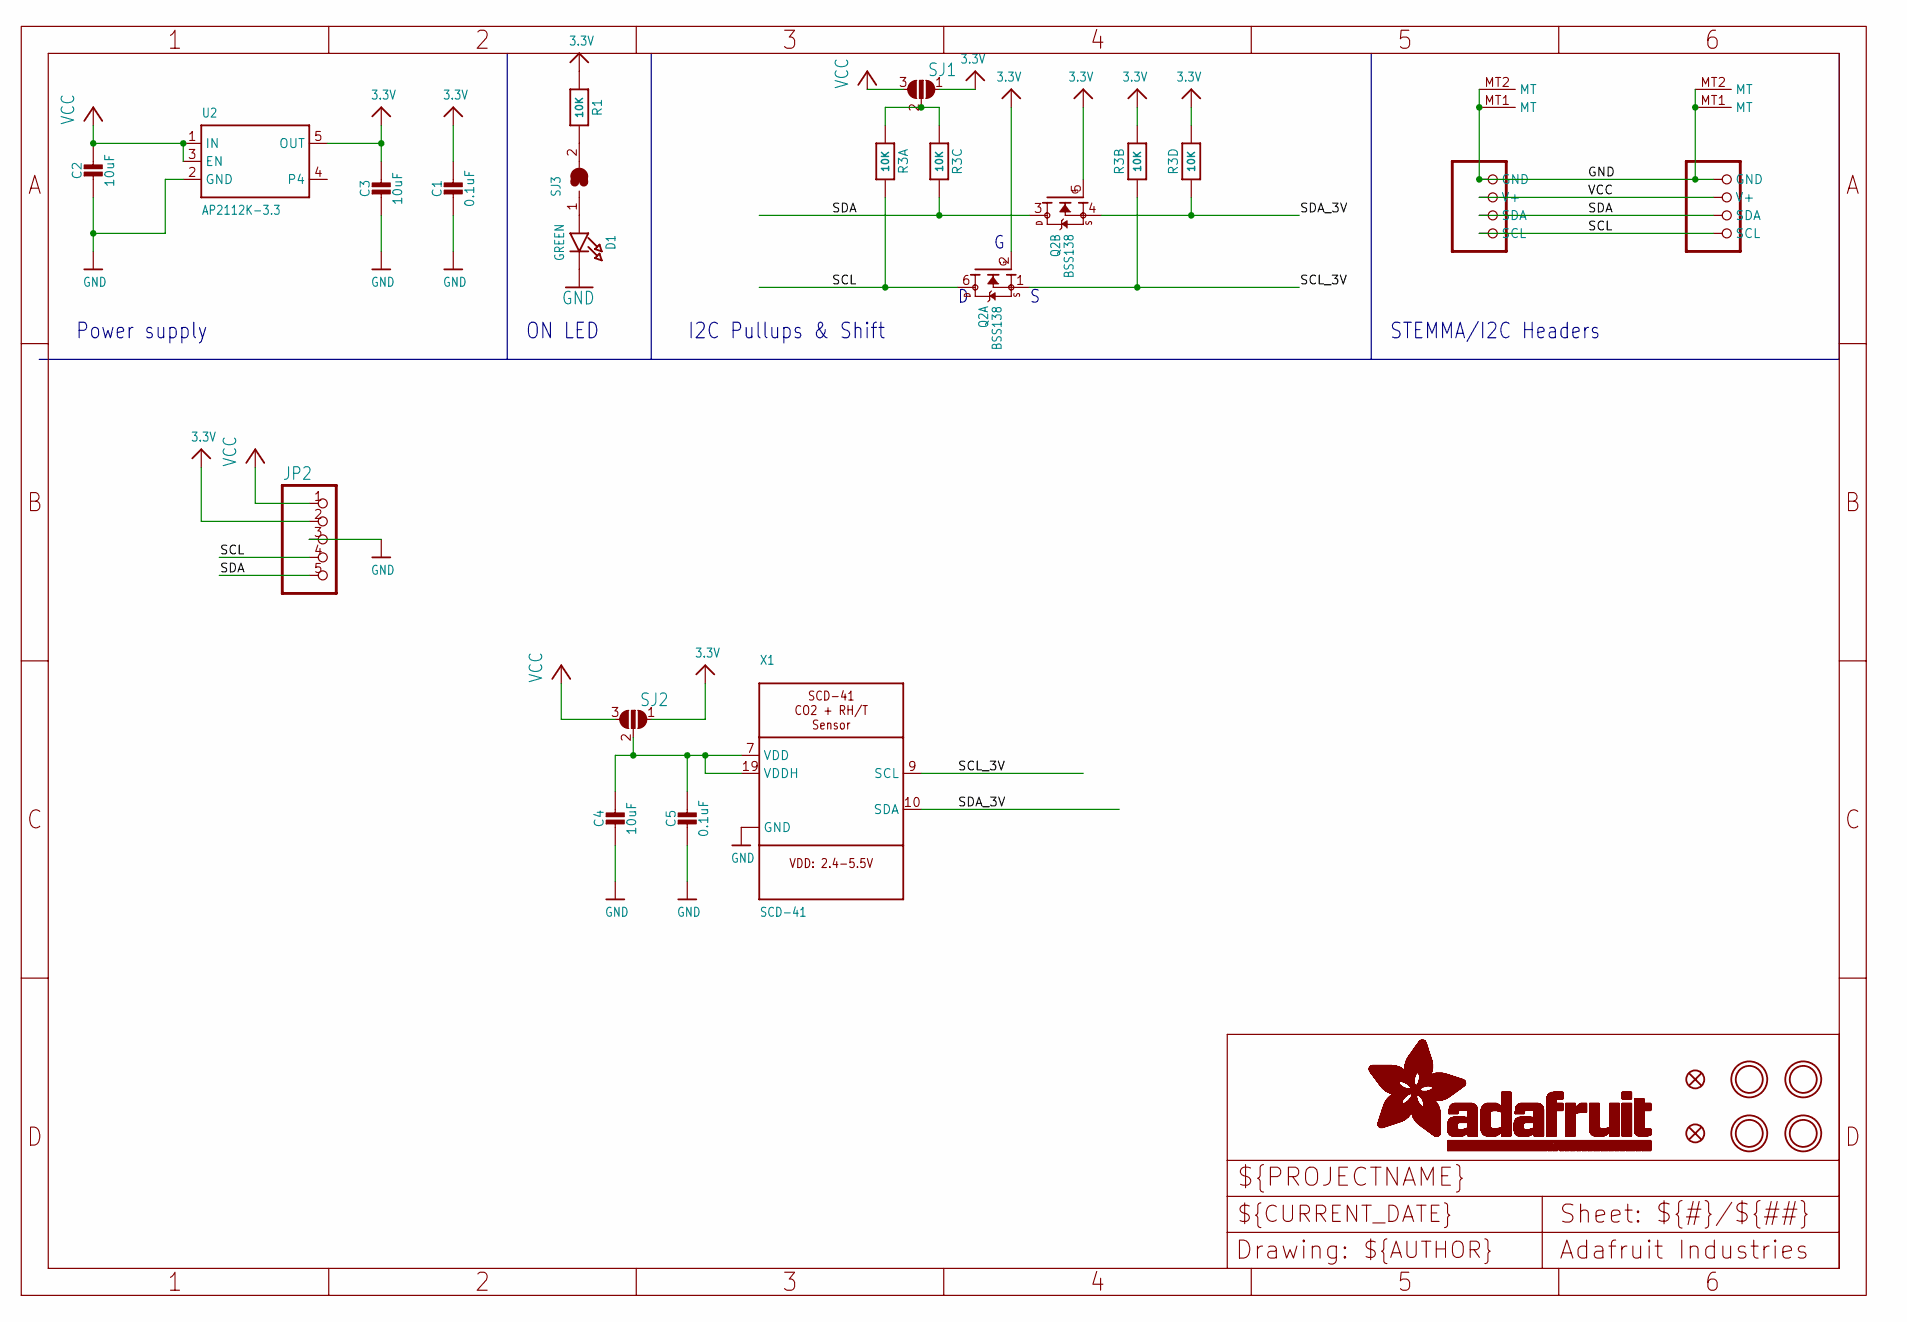
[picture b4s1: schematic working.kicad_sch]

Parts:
C1, C5: 0.1uF; 0603-NO
C2, C3, C4: 10uF; 0805-NO
CONN3, CONN4: STEMMA_I2C_QT; JST_SH4
D1: GREEN; CHIPLED_0603_NOOUTLINE
FID3, FID4: FIDUCIAL_1MM
JP2: HEADER-1X576MIL; 1X05_ROUND_76
Q2: BSS138; SOT363
R1: 10K; 0603-NO
R3: 10K; RESPACK_4X0603
SJ1, SJ2: SOLDERJUMPER_2WAY; SOLDERJUMPER_2WAY_OPEN_NOPASTE
SJ3: SOLDERJUMPERCLOSED; SOLDERJUMPER_CLOSEDWIRE
U2: AP2112K-3.3; SOT23-5
U$1, U$17, U$19, U$21: MOUNTINGHOLE3.0THIN; MOUNTINGHOLE_3.0_PLATEDTHIN
X1: SCD-41; SCD41

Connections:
3.3V: C1.1, C3.1, JP2.2, Q2.2 (G), Q2.5 (G), R1.1, R3.2 (1), R3.4 (1), SJ1.1, SJ2.1, U2.5 (OUT)
GND: C1.2, C2.2, C3.2, C4.2, C5.2, CONN3.1 (GND), CONN3.MT1 (MT), CONN3.MT2 (MT), CONN4.1 (GND), CONN4.MT1 (MT), CONN4.MT2 (MT), D1.C, JP2.3, U2.2 (GND), X1.6 (GND), X1.20 (GND), X1.P$1 (GND)
unnamed: D1.A, SJ3.1
unnamed: R3.1, R3.3 (1), SJ1.2
unnamed: C4.1, C5.1, SJ2.2, X1.7 (VDD), X1.19 (VDDH)
unnamed: R1.2, SJ3.2
SCL: CONN3.4 (SCL), CONN4.4 (SCL), JP2.4, Q2.6 (D), R3.8 (2)
SCL_3V: Q2.1 (S), R3.7 (2), X1.9 (SCL)
SDA: CONN3.3 (SDA), CONN4.3 (SDA), JP2.5, Q2.3 (D), R3.6 (2)
SDA_3V: Q2.4 (S), R3.5 (2), X1.10 (SDA)
VCC: C2.1, CONN3.2 (V+), CONN4.2 (V+), JP2.1, SJ1.3, SJ2.3, U2.1 (IN), U2.3 (EN)

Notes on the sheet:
ON LED
I2C Pullups & Shift
Power supply
STEMMA/I2C Headers

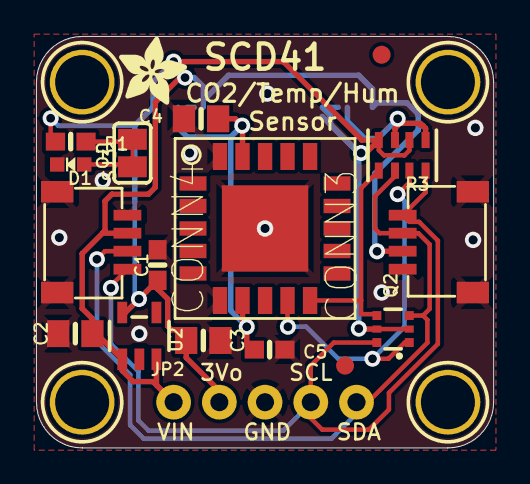
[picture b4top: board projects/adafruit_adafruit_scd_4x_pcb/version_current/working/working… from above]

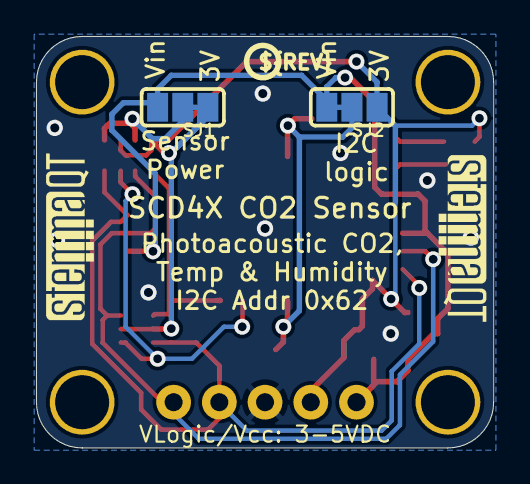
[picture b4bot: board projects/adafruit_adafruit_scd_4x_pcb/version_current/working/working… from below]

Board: 2 copper layers, 25.4 x 22.9 mm, 27 parts (5 on the bottom side), 11 nets.

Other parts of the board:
U$22: ADAFRUIT_3.5MM
U$25: PCBFEAT-REV-040
U$30, U$31: STEMMAQT

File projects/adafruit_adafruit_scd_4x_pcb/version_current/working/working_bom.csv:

Row,Description,Part,References,Value,Footprint,Quantity Per PCB,Status,Datasheet
1,,CAP_CERAMIC0603_NO,C1 C5,0.1uF,0603-NO,2, ,
2,,CAP_CERAMIC0805-NOOUTLINE,C2 C3 C4,10uF,0805-NO,3, ,
3,,STEMMA_I2C_QT,CONN3 CONN4,STEMMA_I2C_QT,JST_SH4,2, ,
4,,LED0603_NOOUTLINE,D1,GREEN,CHIPLED_0603_NOOUTLINE,1, ,
5,,HEADER-1X576MIL,JP2,HEADER-1X576MIL,1X05_ROUND_76,1, ,
6,,MOSFET-N_DUAL,Q2,BSS138,SOT363,1, ,
7,,RESISTOR_0603_NOOUT,R1,10K,0603-NO,1, ,
8,,RESISTOR_4PACK,R3,10K,RESPACK_4X0603,1, ,
9,,VREG_SOT23-5,U2,AP2112K-3.3,SOT23-5,1, ,
10,,SCD-41,X1,SCD-41,SCD41,1, ,





Project info:
Schematic:,working
Variant:,default
Revision:,
Date:,2023-08-03_17-21-23
KiCad Version:,7.0.6-7.0.6~ubuntu22.04.1
Statistics:
Component Groups:,10
Component Count:,14 (0 SMD/ 0 THT)
Fitted Components:,14 (0 SMD/ 0 THT)
Number of PCBs:,1
Total Components:,14
